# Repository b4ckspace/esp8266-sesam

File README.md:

# esp8266-sesam

Universal Wifi door opener. 

A project by [schinken](https://github.com/schinken "schinkens Github") and [xoquox](https://github.com/xoquox "xoquoxs Github")

# Hardware

Our hardware works with a ESP-07 or ESP-12e modul. It uses nice little DIL relays, becaus we can direct control them with TTL-signals. What I think is very nice for a relay. 

# Webinterface
  TODO

# REST-API
  TODO

# License
  TODOh

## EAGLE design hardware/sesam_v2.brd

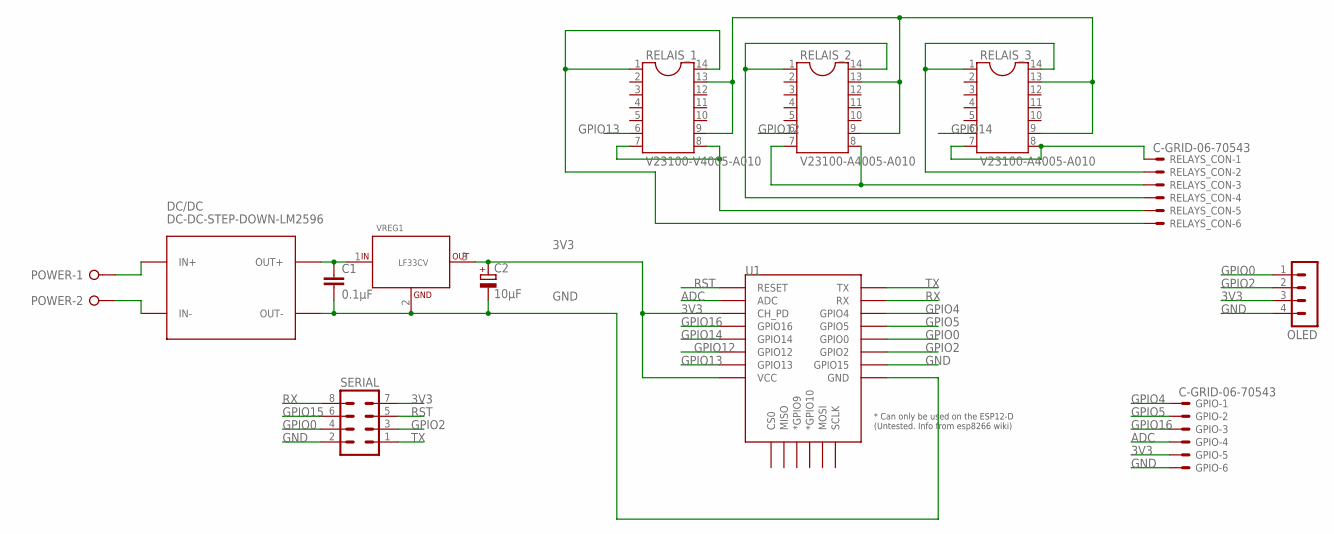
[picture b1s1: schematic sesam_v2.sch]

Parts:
C1: 0.1µF; C0805
C2: 10µF; E2-5
DC/DC: DC-DC-STEP-DOWN-LM2596
GPIO: C-GRID-06-70543; 70543-06
OLED: MA04-1
POWER: W237-02P; W237-132
RELAIS_1: V23100-V4005-A010; SOCKET-14
RELAIS_2, RELAIS_3: V23100-A4005-A010; SOCKET-14
RELAYS_CON: C-GRID-06-70543; 70543-06
SERIAL: MA04-2
U1: ESP12ESMD; ESP12E-SMD
VREG1: LF33CV; TO220

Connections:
3V3: C2.+, GPIO.5, OLED.3, SERIAL.7, U1.CH_PD, U1.VCC, VREG1.3 (OUT)
ADC: GPIO.4, U1.ADC
GND: C1.2, C2.-, DC/DC.IN-, DC/DC.OUT-, GPIO.6, OLED.4, POWER.2, RELAIS_1.9, RELAIS_1.13, RELAIS_2.9, RELAIS_2.13, RELAIS_3.9, RELAIS_3.13, SERIAL.2, U1.GND, U1.GPIO15, VREG1.2 (GND)
GPIO0: OLED.1, SERIAL.4, U1.GPIO0
GPIO2: OLED.2, SERIAL.3, U1.GPIO2
GPIO4: GPIO.1, U1.GPIO4
GPIO5: GPIO.2, U1.GPIO5
GPIO12: RELAIS_2.6, U1.GPIO12
GPIO13: RELAIS_1.6, U1.GPIO13
GPIO14: RELAIS_3.6, U1.GPIO14
GPIO15: SERIAL.6
GPIO16: GPIO.3, U1.GPIO16
unnamed: RELAIS_3.1, RELAIS_3.14, RELAYS_CON.2
unnamed: DC/DC.IN+, POWER.1
unnamed: RELAIS_3.7, RELAIS_3.8, RELAYS_CON.1
unnamed: RELAIS_2.1, RELAIS_2.14, RELAYS_CON.4
unnamed: RELAIS_2.7, RELAIS_2.8, RELAYS_CON.3
unnamed: RELAIS_1.1, RELAIS_1.14, RELAYS_CON.6
unnamed: RELAIS_1.7, RELAIS_1.8, RELAYS_CON.5
POWER: C1.1, DC/DC.OUT+, VREG1.1 (IN)
RST: SERIAL.5, U1.RESET
RX: SERIAL.8, U1.RXD0 (RX)
TX: SERIAL.1, U1.TXD0 (TX)

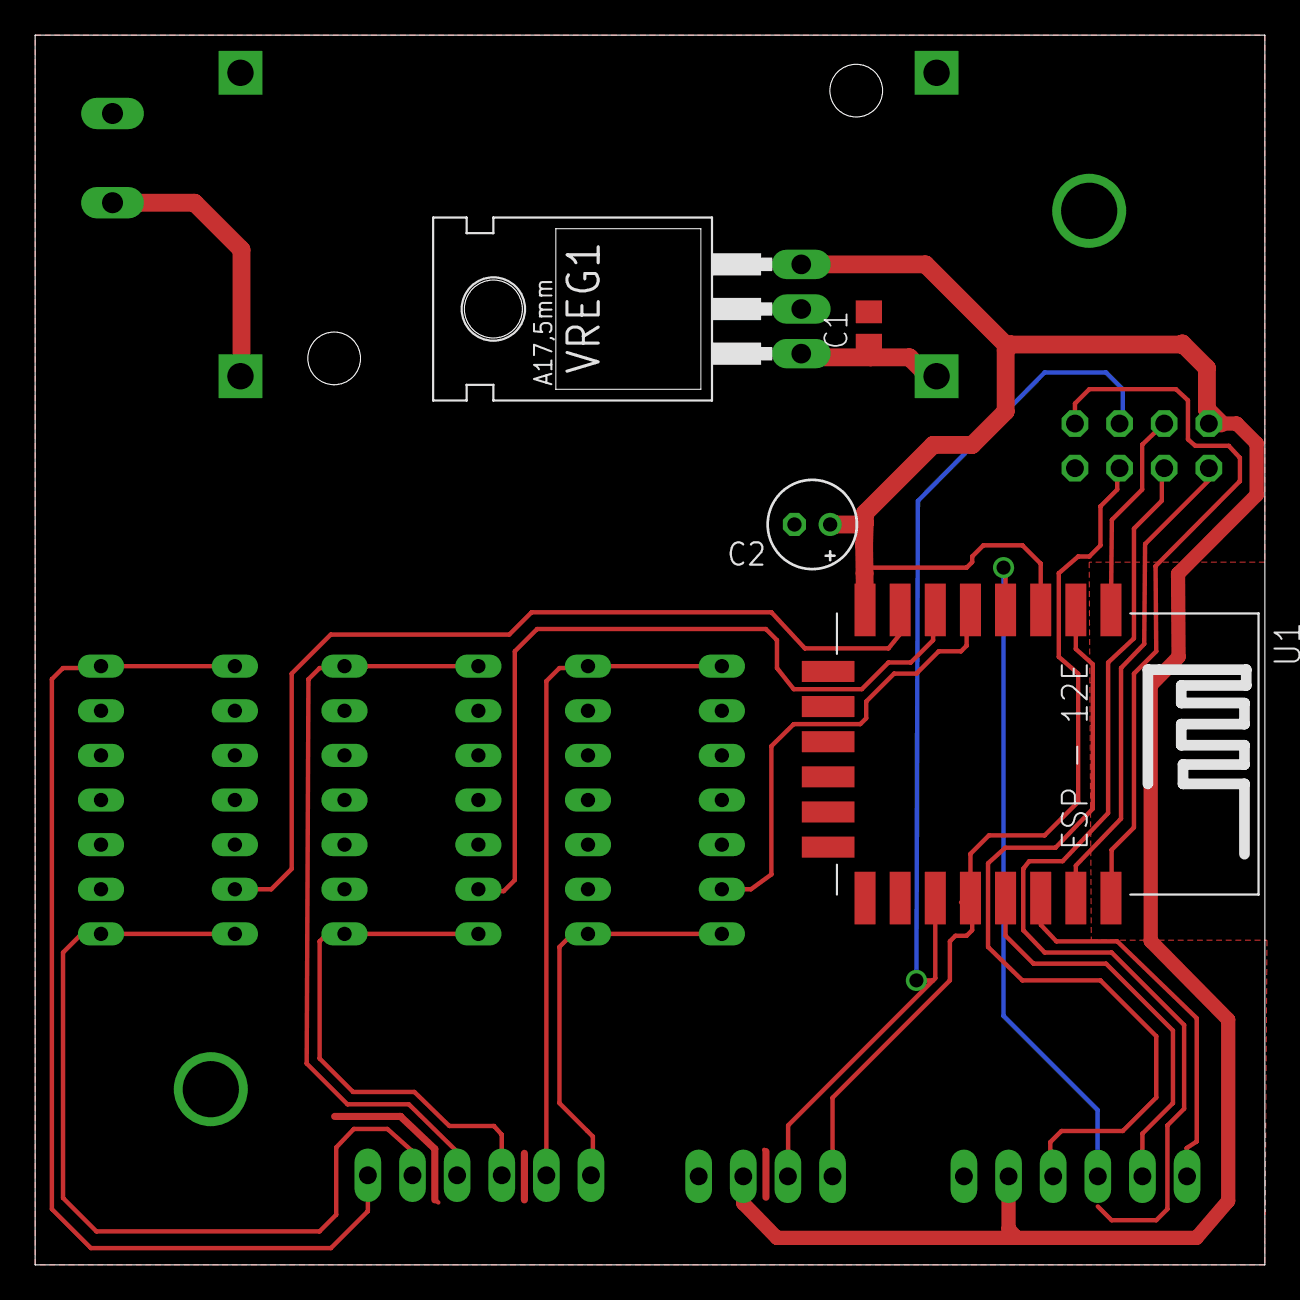
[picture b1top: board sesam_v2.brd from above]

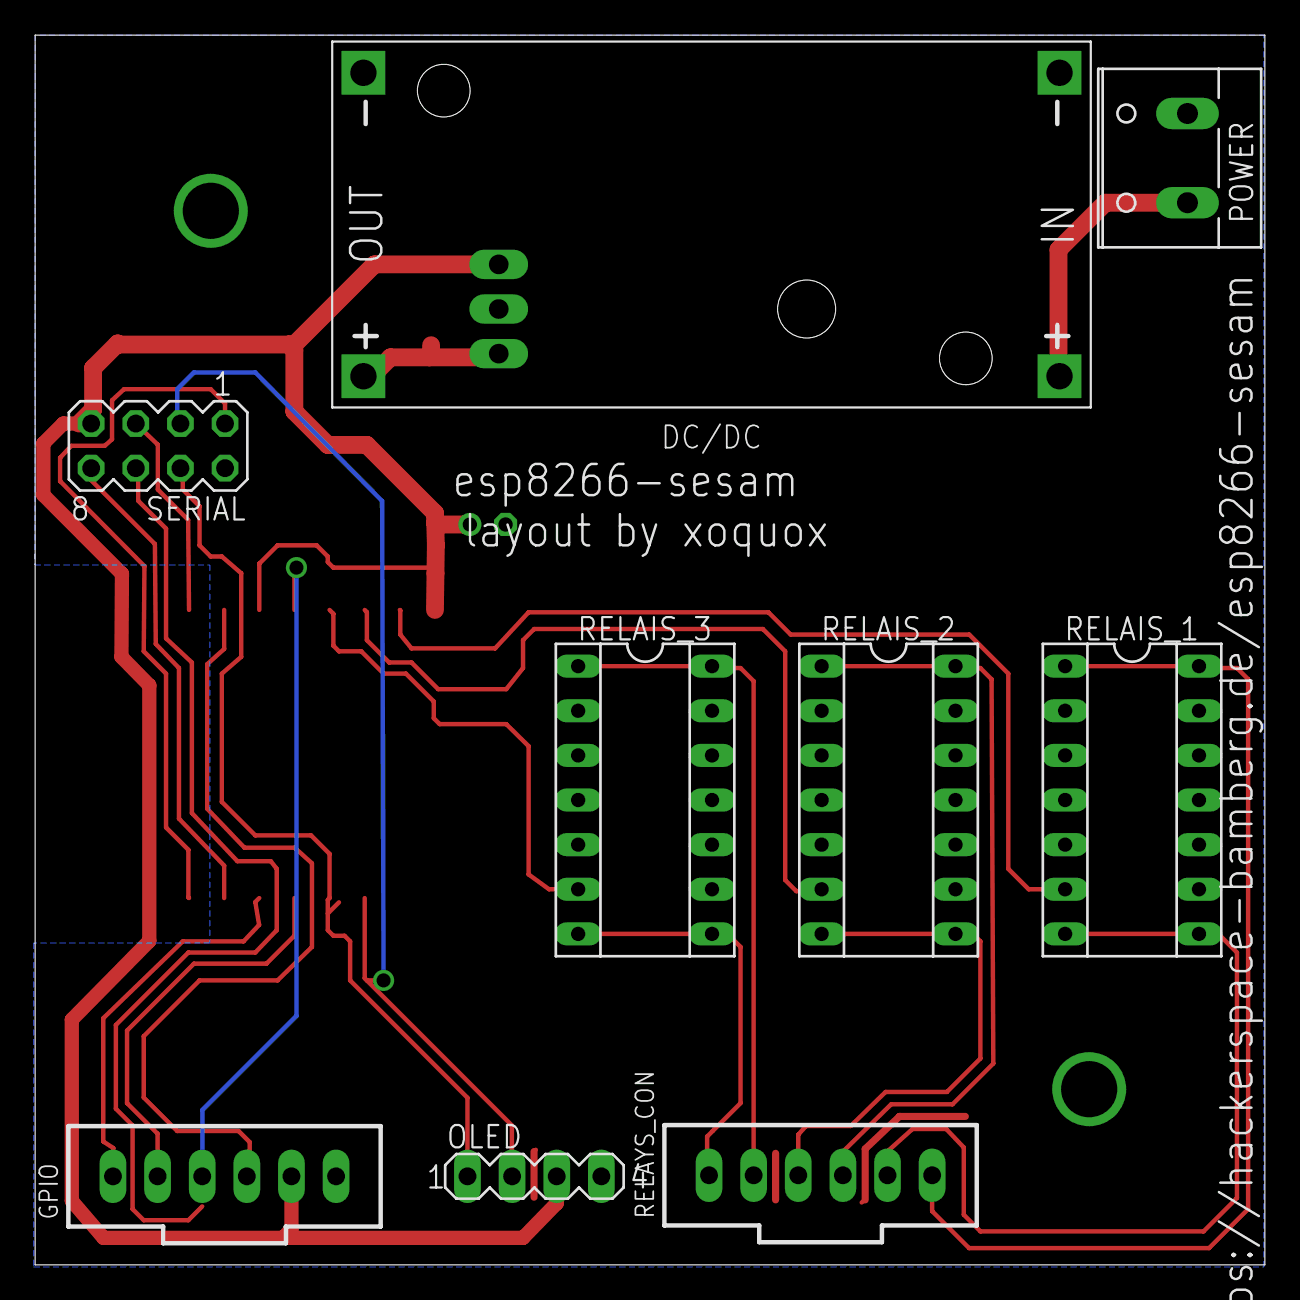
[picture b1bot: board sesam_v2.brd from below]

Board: 2 copper layers, 70.0 x 70.0 mm, 13 parts (9 on the bottom side), 22 nets.

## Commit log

2016-05-22 switched to the correct regulator
2016-05-22 Display added, WIFI changed from AP to Client
2016-05-23 display output optimized
2016-05-24 minor tweaks of the board and change of display text size
2016-05-25 Add license
2016-05-28 wrong esp modul in README.md

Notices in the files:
parts and their libraries:
diy-modules: Released under the Creative Commons Attribution 4.0 International License: http://creativecommons.org/licenses/by/4.0
